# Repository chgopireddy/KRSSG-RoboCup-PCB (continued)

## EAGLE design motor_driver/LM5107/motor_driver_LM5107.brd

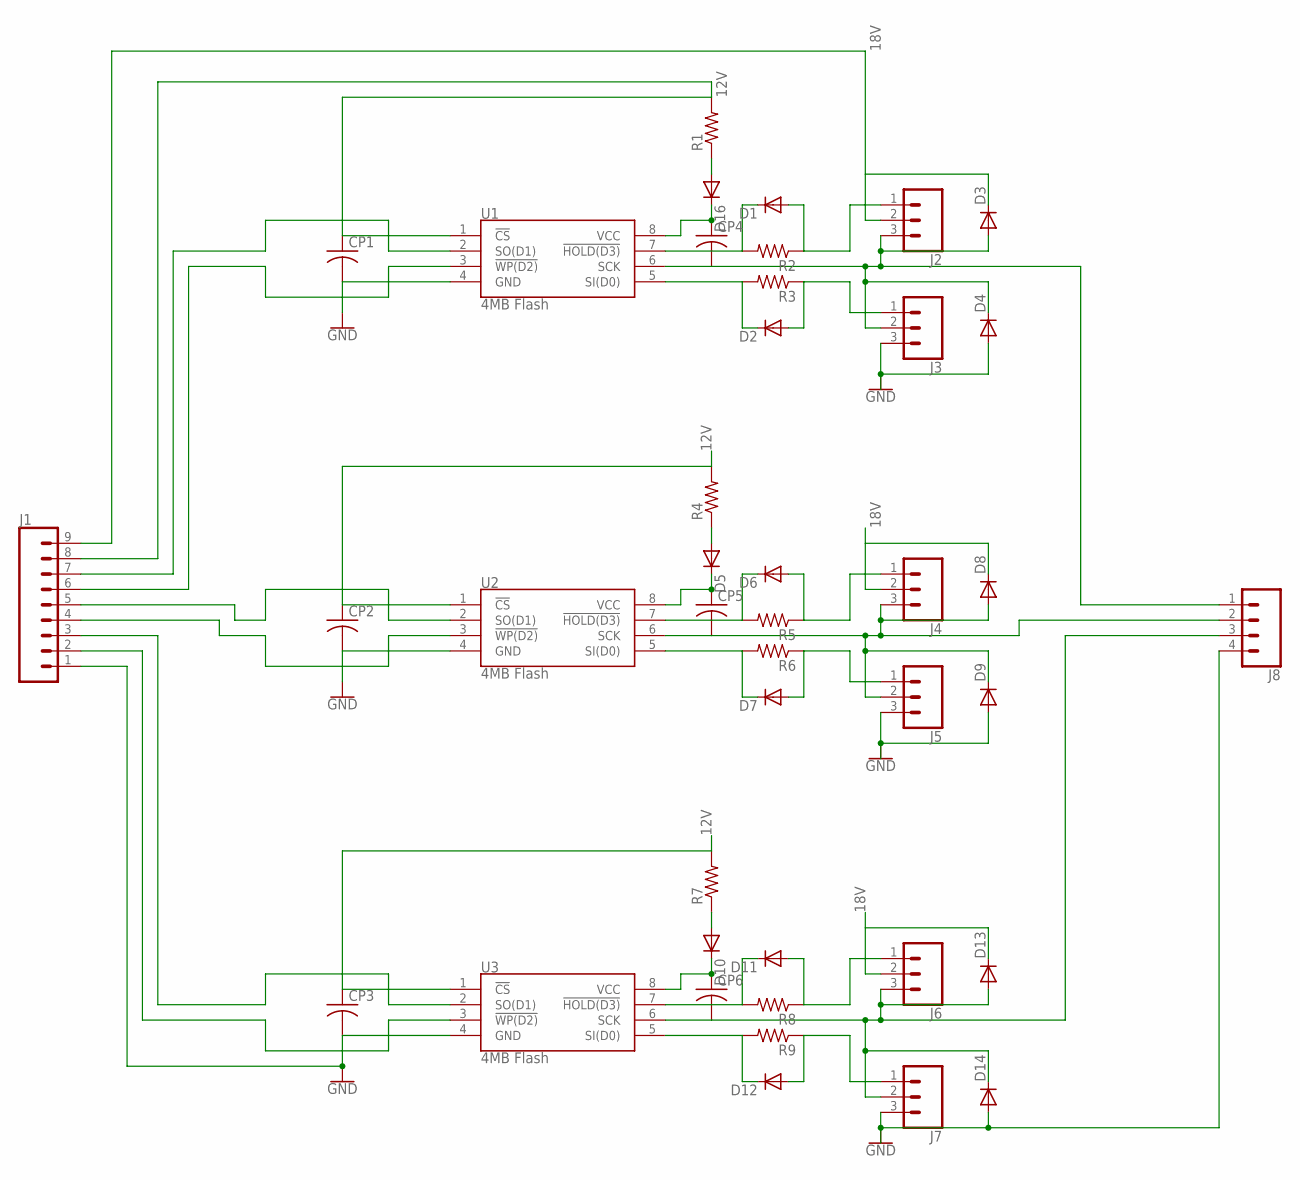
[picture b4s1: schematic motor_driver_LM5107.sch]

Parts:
CP1, CP2, CP3, CP4, CP5, CP6: C-US025-024X044; C025-024X044
D1, D2, D3, D4, D5, D6, D7, D8, D9, D10, D11, D12, D13, D14, D16: DIODE-D-5; D-5
J1: CONN_09; 1X09
J2, J3, J4, J5, J6, J7: CONN_03LOCK; 1X03_LOCK
J8: CONN_04; 1X04
R1, R2, R3, R4, R5, R6, R7, R8, R9: R-US_0204/5; 0204/5
U1, U2, U3: 4MB Flash; SO08

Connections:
12V: CP1.1, CP2.1, CP3.1, J1.8, R1.2, R4.2, R7.2, U1.1 (!CS), U2.1 (!CS), U3.1 (!CS)
18V: D3.C, D8.C, D13.C, J1.9, J2.2, J4.2, J6.2
GND: CP1.2, CP2.2, CP3.2, D4.A, D9.A, D14.A, J1.1, J3.3, J5.3, J7.3, J8.4, U1.4 (GND), U2.4 (GND), U3.4 (GND)
unnamed: D16.A, R1.1
unnamed: CP4.1, D16.C, U1.8 (VCC)
unnamed: D1.C, R2.2, U1.7 (!HOLD(D3))
unnamed: CP4.2, D3.A, D4.C, J2.3, J3.2, J8.1, U1.6 (SCK)
unnamed: J1.7, U1.2 (SO(D1))
unnamed: J1.6, U1.3 (!WP(D2))
unnamed: D2.C, R3.2, U1.5 (SI(D0))
unnamed: D1.A, J2.1, R2.1
unnamed: D2.A, J3.1, R3.1
unnamed: D5.A, R4.1
unnamed: CP5.1, D5.C, U2.8 (VCC)
unnamed: CP5.2, D8.A, D9.C, J4.3, J5.2, J8.2, U2.6 (SCK)
unnamed: J1.5, U2.2 (SO(D1))
unnamed: J1.4, U2.3 (!WP(D2))
unnamed: D6.C, R5.2, U2.7 (!HOLD(D3))
unnamed: D7.C, R6.2, U2.5 (SI(D0))
unnamed: D6.A, J4.1, R5.1
unnamed: D7.A, J5.1, R6.1
unnamed: D10.A, R7.1
unnamed: CP6.1, D10.C, U3.8 (VCC)
unnamed: CP6.2, D13.A, D14.C, J6.3, J7.2, J8.3, U3.6 (SCK)
unnamed: J1.3, U3.2 (SO(D1))
unnamed: J1.2, U3.3 (!WP(D2))
unnamed: D11.C, R8.2, U3.7 (!HOLD(D3))
unnamed: D12.C, R9.2, U3.5 (SI(D0))
unnamed: D11.A, J6.1, R8.1
unnamed: D12.A, J7.1, R9.1

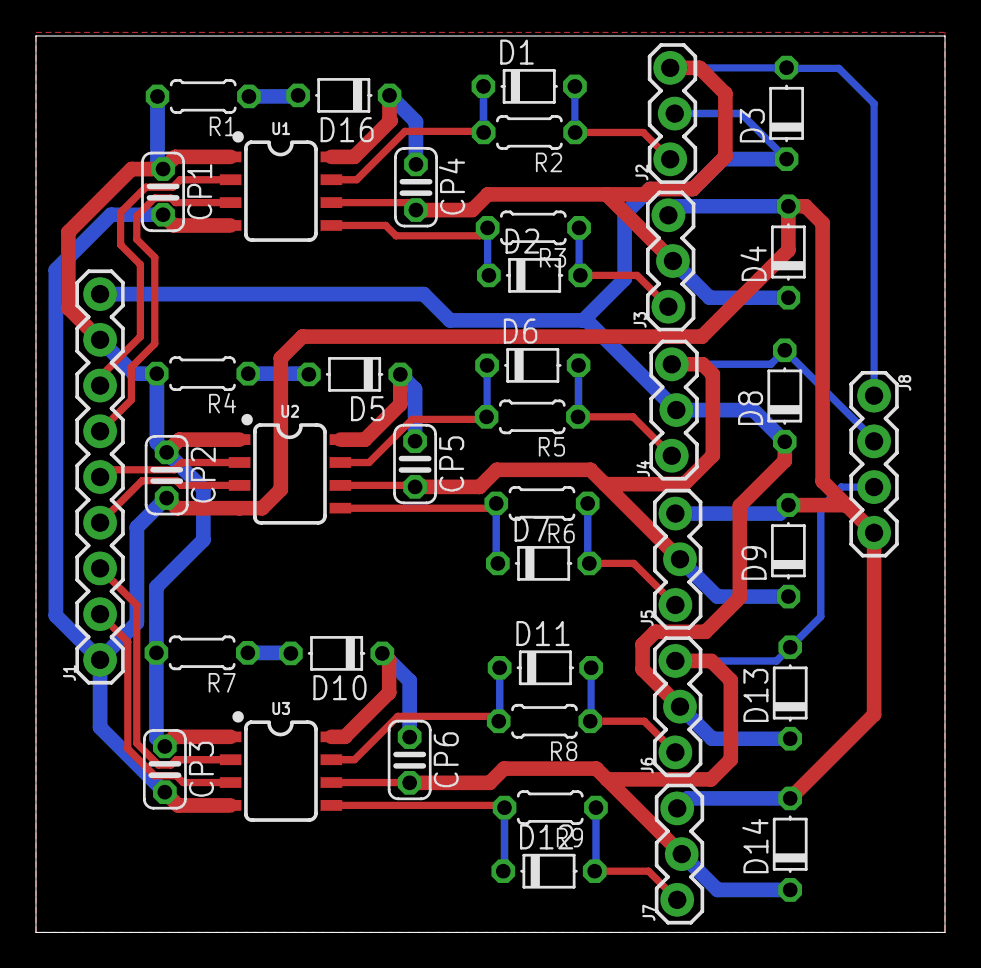
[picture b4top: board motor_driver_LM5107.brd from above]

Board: 2 copper layers, 50.5 x 49.8 mm, 41 parts (0 on the bottom side), 30 nets.

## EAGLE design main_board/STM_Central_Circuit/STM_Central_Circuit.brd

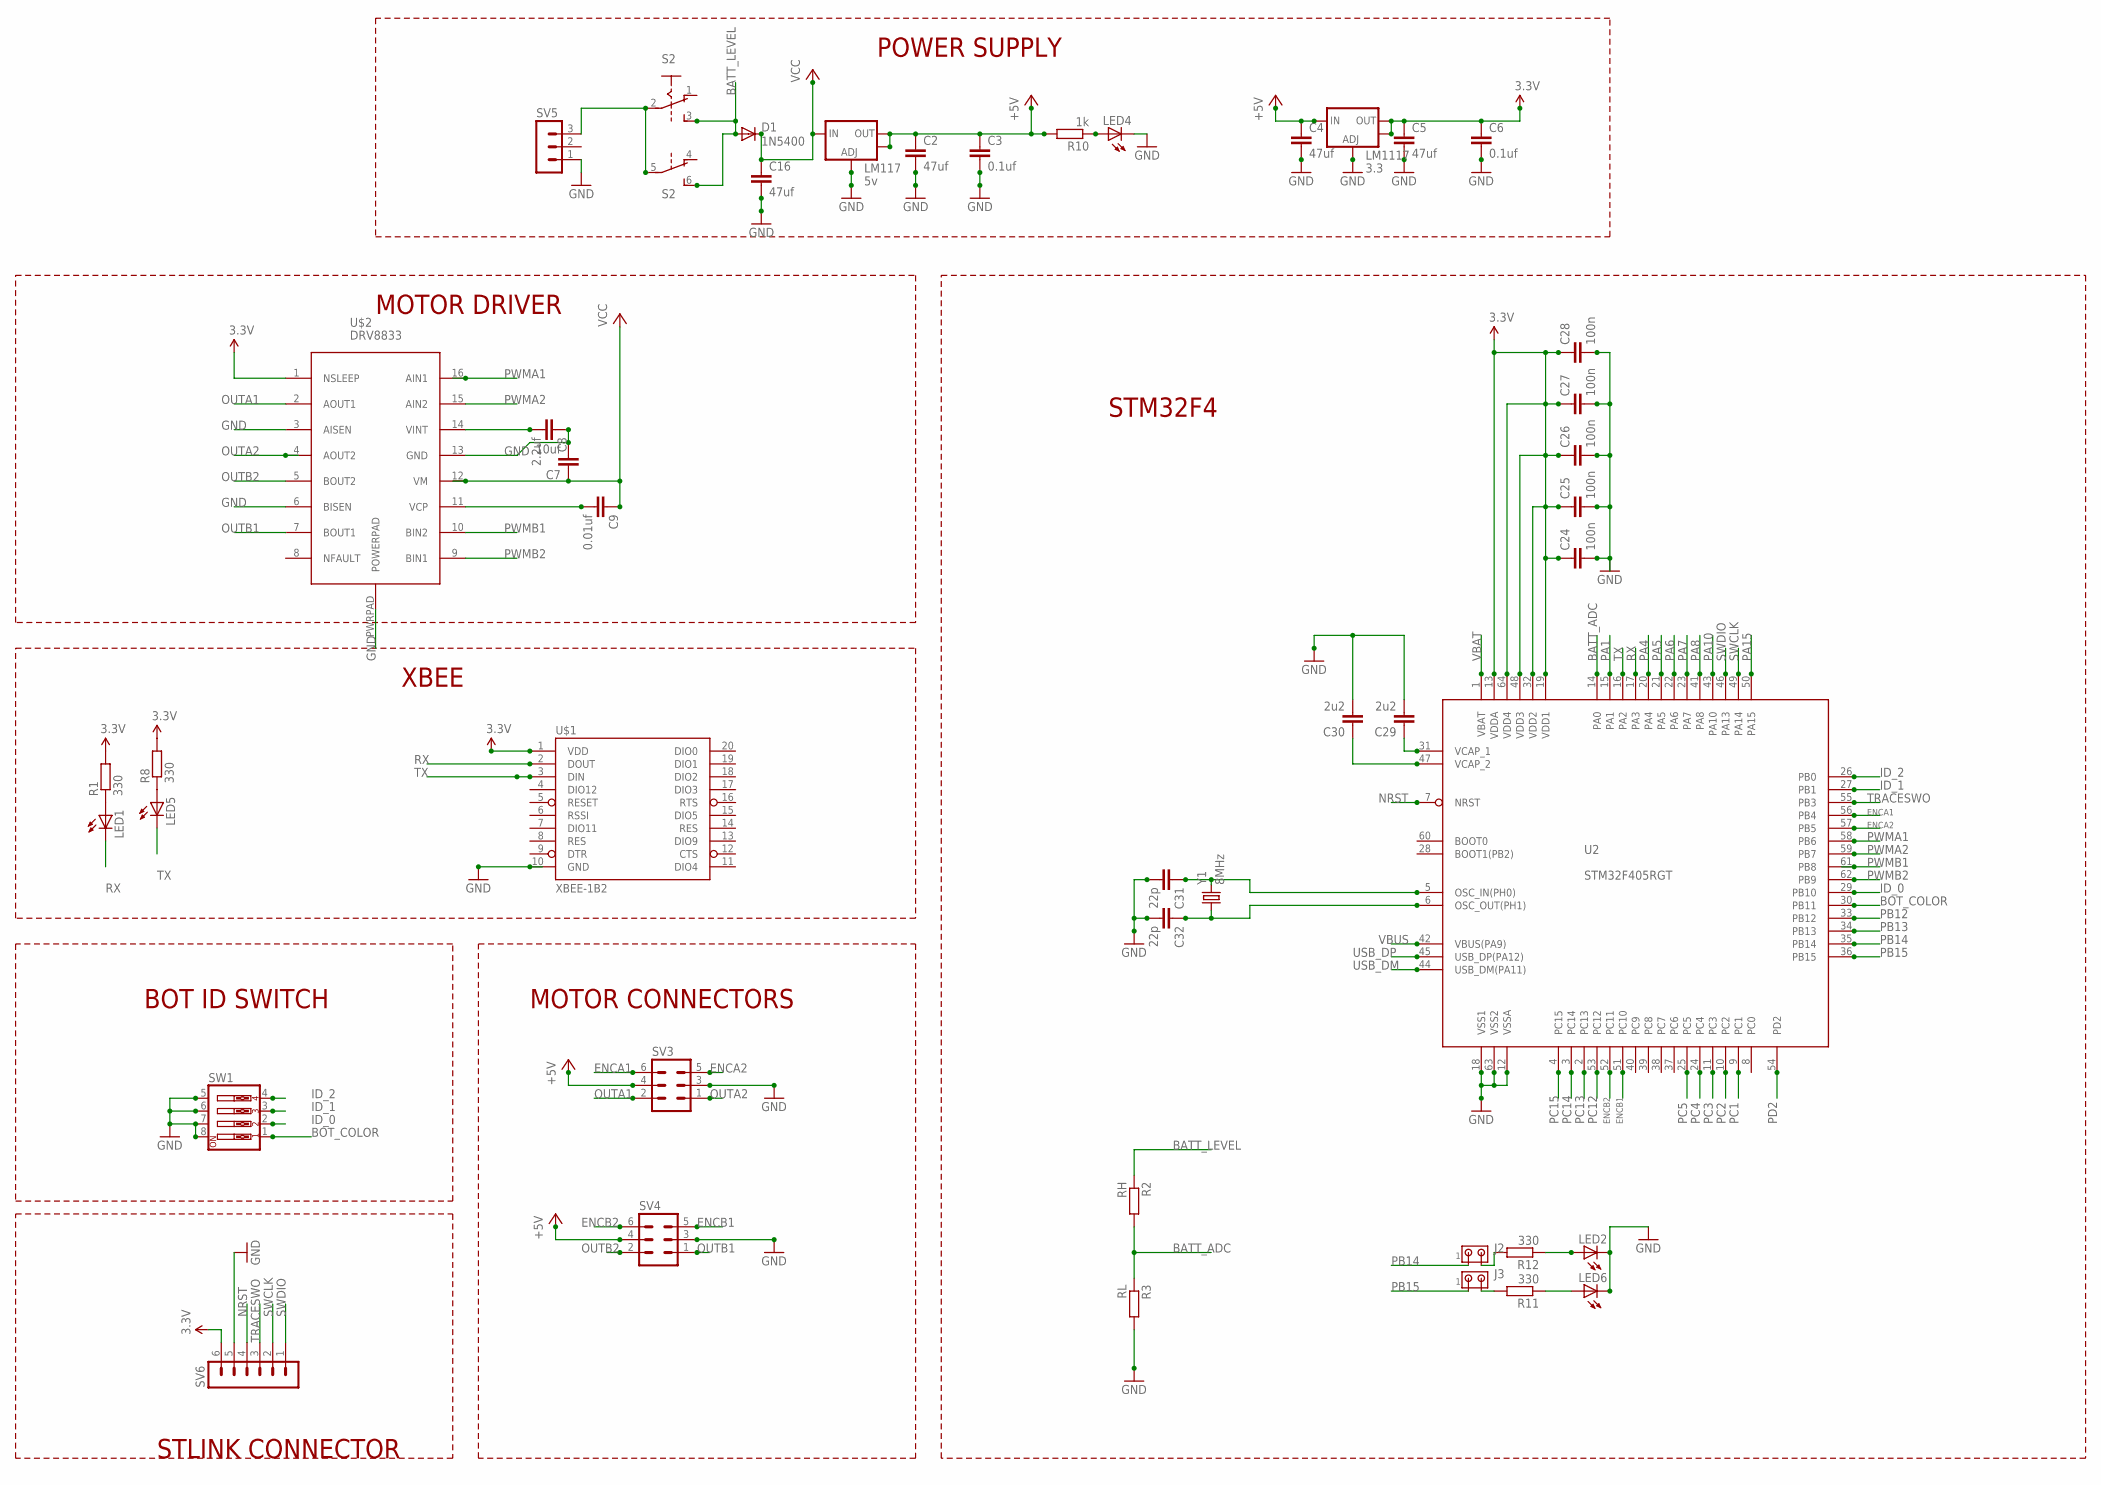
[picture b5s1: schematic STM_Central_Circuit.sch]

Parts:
C2, C4, C5, C16: 47uf; C1206
C3, C6: 0.1uf; C1206
C7: 10uf; C1206
C8: 2.2uf; C1206
C9: 0.01uf; C1206
C24, C25, C26, C27, C28: 100n; 0603-CAP
C29, C30: 2u2; 0603-CAP
C31, C32: 22p; 0603-CAP
D1: 1N5400; DO201-15
J2, J3: MTA02-100; 10X02MTA
LED1, LED2, LED4, LED5, LED6: LED5MM
LM117: 5v; SOT223
LM1117: 3.3; SOT223
R1, R8, R11, R12: 330; 0207/10
R2: RH; 0207/10
R3: RL; 0207/10
R10: 1k; 0207/10
S2: A68-A31
SV3, SV4: MA03-2
SV5: MA03-1
SV6: MA06-1
SW1: SW_DIP-4; EDG-04
U2: STM32F405RGT; LQFP64
U$1: XBEE-1B2; XBEE-SILK
U$2: DRV8833; PWP_R_PDSO_G16
Y1: 8MHz; CRYSTAL-SMD-5X3

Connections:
3.3V: C5.1, C6.1, C24.1, C25.1, C26.1, C27.1, C28.1, LM1117.2 (OUT), LM1117.4 (OUT), R1.2, R8.2, SV6.6, U2.13 (VDDA), U2.19 (VDD1), U2.32 (VDD2), U2.48 (VDD3), U2.64 (VDD4), U$1.1 (VDD), U$2.1 (NSLEEP)
+5V: C2.1, C3.1, C4.1, LM117.2 (OUT), LM117.4 (OUT), LM1117.3 (IN), R10.2, SV3.4, SV4.4
BATT_ADC: R2.2, R3.1, U2.14 (PA0)
BATT_LEVEL: D1.A, R2.1, S2.3 (S), S2.6 (S)
BOT_COLOR: SW1.1, U2.30 (PB11)
ENCA1: SV3.6, U2.56 (PB4)
ENCA2: SV3.5, U2.57 (PB5)
ENCB1: SV4.5, U2.51 (PC10)
ENCB2: SV4.6, U2.52 (PC11)
GND: C2.2, C3.2, C4.2, C5.2, C6.2, C7.2, C8.1, C16.2, C24.2, C25.2, C26.2, C27.2, C28.2, C29.2, C30.2, C31.2, C32.2, LED2.K (C), LED4.K (C), LED6.K (C), LM117.1 (ADJ), LM1117.1 (ADJ), R3.2, SV3.3, SV4.3, SV5.1, SV6.5, SW1.5, SW1.6, SW1.7, SW1.8, U2.12 (VSSA), U2.18 (VSS1), U2.63 (VSS2), U$1.10 (GND), U$2.3 (AISEN), U$2.6 (BISEN), U$2.13 (GND), U$2.PWRPAD (POWERPAD)
ID_0: SW1.2, U2.29 (PB10)
ID_1: SW1.3, U2.27 (PB1)
ID_2: SW1.4, U2.26 (PB0)
unnamed: LED1.A, R1.1
unnamed: LED6.A, R11.1
unnamed: J2.2, R12.2
unnamed: LED4.A, R10.1
unnamed: LED5.A, R8.1
unnamed: C8.2, U$2.14 (VINT)
unnamed: J3.2, R11.2
unnamed: LED2.A, R12.1
unnamed: S2.2, S2.5, SV5.3
unnamed: C9.2, U$2.11 (VCP)
unnamed: C29.1, U2.31 (VCAP_1)
unnamed: C30.1, U2.47 (VCAP_2)
unnamed: C32.1, U2.6 (OSC_OUT(PH1)), Y1.1
unnamed: C31.1, U2.5 (OSC_IN(PH0)), Y1.3 (2)
NRST: SV6.4, U2.7 (NRST)
OUTA1: SV3.2, U$2.2 (AOUT1)
OUTA2: SV3.1, U$2.4 (AOUT2)
OUTB1: SV4.1, U$2.7 (BOUT1)
OUTB2: SV4.2, U$2.5 (BOUT2)
PA1: U2.15 (PA1)
PA4: U2.20 (PA4)
PA5: U2.21 (PA5)
PA6: U2.22 (PA6)
PA7: U2.23 (PA7)
PA8: U2.41 (PA8)
PA10: U2.43 (PA10)
PA15: U2.50 (PA15)
PB12: U2.33 (PB12)
PB13: U2.34 (PB13)
PB14: J2.1, U2.35 (PB14)
PB15: J3.1, U2.36 (PB15)
PC1: U2.9 (PC1)
PC2: U2.10 (PC2)
PC3: U2.11 (PC3)
PC4: U2.24 (PC4)
PC5: U2.25 (PC5)
PC12: U2.53 (PC12)
PC13: U2.2 (PC13)
PC14: U2.3 (PC14)
PC15: U2.4 (PC15)
PD2: U2.54 (PD2)
PWMA1: U2.58 (PB6), U$2.16 (AIN1)
PWMA2: U2.59 (PB7), U$2.15 (AIN2)
PWMB1: U2.61 (PB8), U$2.10 (BIN2)
PWMB2: U2.62 (PB9), U$2.9 (BIN1)
RX: LED1.K (C), U2.17 (PA3), U$1.2 (DOUT)
SWCLK: SV6.2, U2.49 (PA14)
SWDIO: SV6.1, U2.46 (PA13)
TRACESWO: SV6.3, U2.55 (PB3)
TX: LED5.K (C), U2.16 (PA2), U$1.3 (DIN)
USB_DM: U2.44 (USB_DM(PA11))
USB_DP: U2.45 (USB_DP(PA12))
VBAT: U2.1 (VBAT)
VBUS: U2.42 (VBUS(PA9))
VCC: C7.1, C9.1, C16.1, D1.C, LM117.3 (IN), U$2.12 (VM)

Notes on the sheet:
BOT ID SWITCH
MOTOR CONNECTORS
XBEE
MOTOR DRIVER
STM32F4
POWER SUPPLY
STLINK CONNECTOR

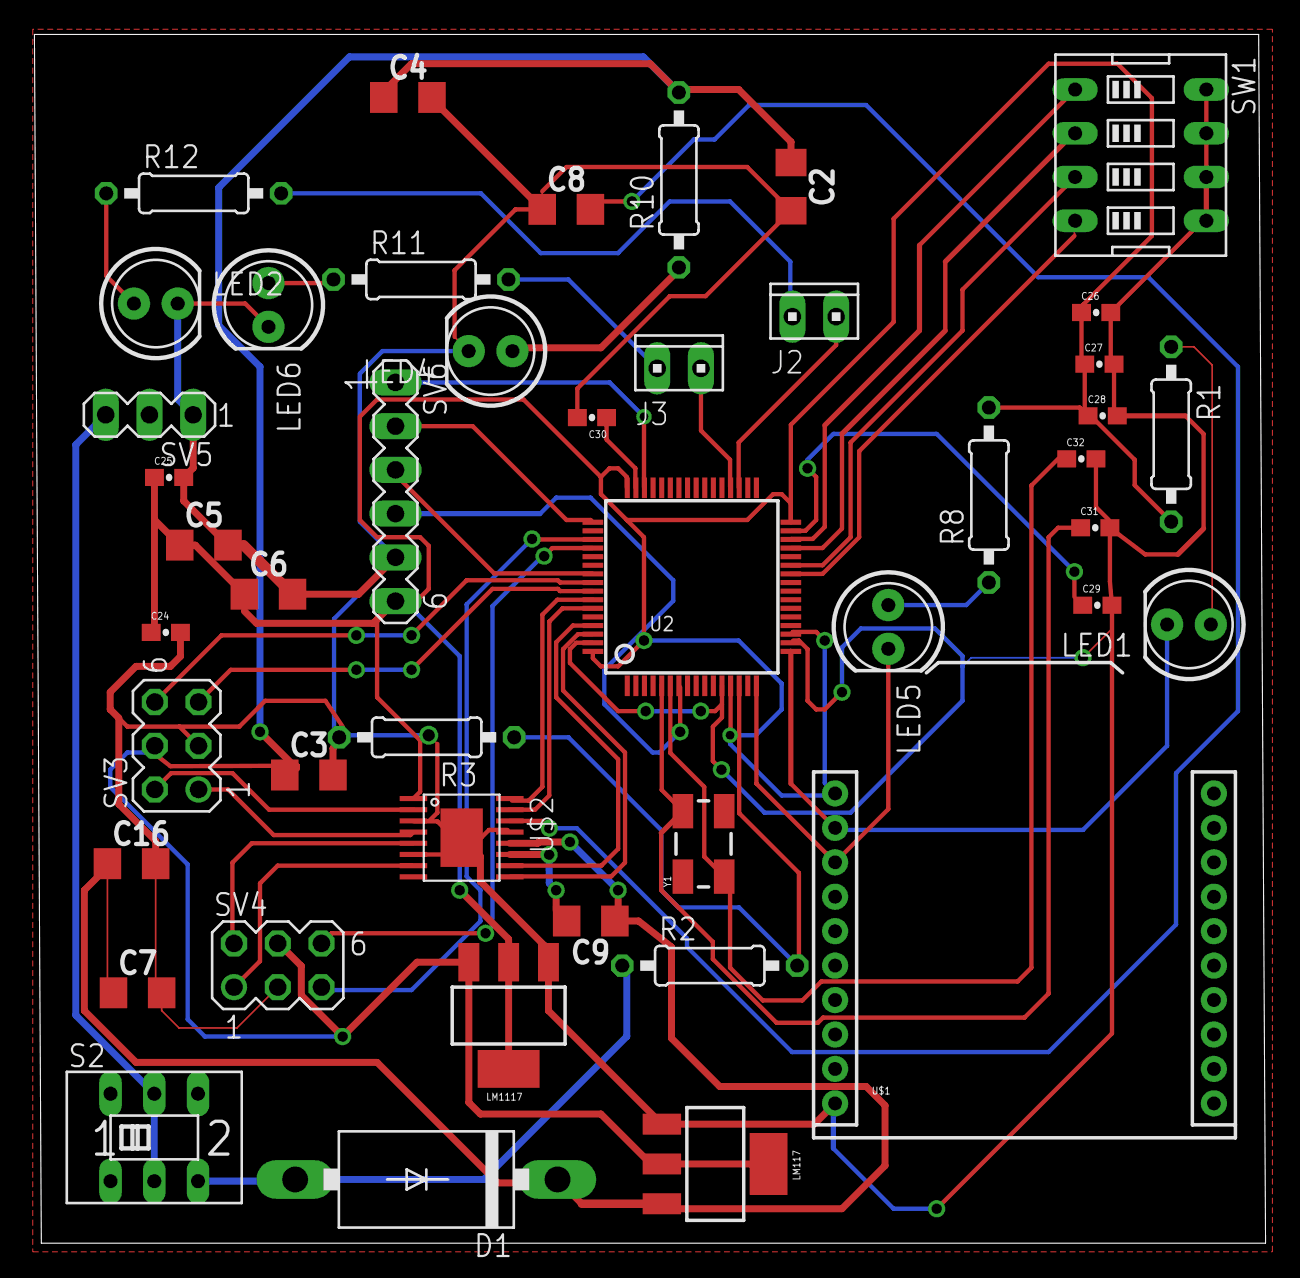
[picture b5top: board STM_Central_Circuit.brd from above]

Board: 2 copper layers, 71.5 x 70.2 mm, 45 parts (0 on the bottom side), 44 nets.

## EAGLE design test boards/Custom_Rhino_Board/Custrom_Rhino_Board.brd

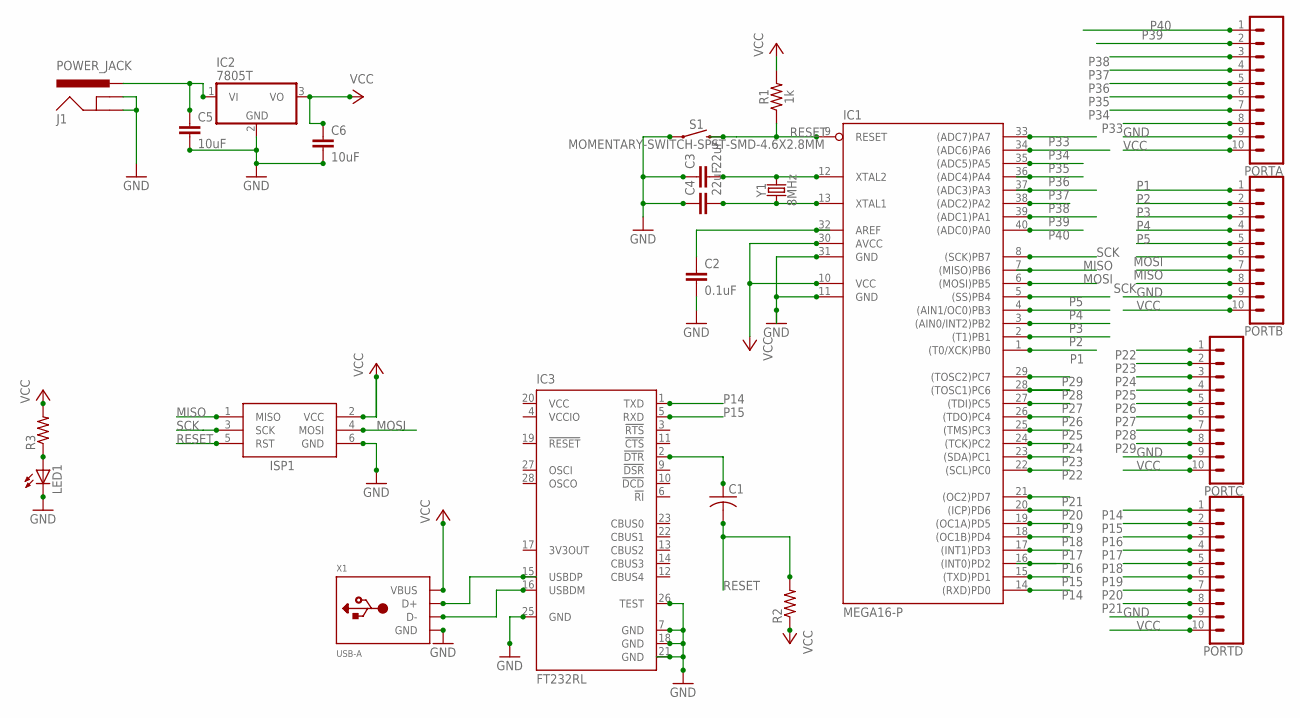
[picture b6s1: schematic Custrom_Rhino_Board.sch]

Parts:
C1: C-US025-024X044; C025-024X044
C2: 0.1uF; 0603
C3, C4: 22uF; 0805
C5, C6: 10uF; 0805
IC1: MEGA16-P; DIL40
IC2: 7805T; TO220H
IC3: FT232RL; SSOP28
ISP1: AVRISP-6; AVRISP
J1: POWER_JACK; POWER_JACK_PTH
LED1: LEDCHIP-LED0603; CHIP-LED0603
PORTA: CONN_10"; 1X10
PORTB: CONN_10"; 1X10
PORTC: CONN_10"; 1X10
PORTD: CONN_10"; 1X10
R1: 1k; AXIAL-0.3
R2, R3: R-US_0204/5; 0204/5
S1: MOMENTARY-SWITCH-SPST-SMD-4.6X2.8MM; TACTILE_SWITCH_SMD_4.6X2.8MM
X1: USB-A; MOLEX_480371000
Y1: 8MHz; HC49UP

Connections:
GND: C2.2, C3.1, C4.1, C5.2, C6.2, IC1.11 (GND), IC1.31 (GND), IC2.2 (GND), IC3.7 (GND), IC3.18 (GND), IC3.21 (GND), IC3.25 (GND), IC3.26 (TEST), ISP1.6 (GND), J1.GND, J1.GNDBREAK, LED1.C, PORTA.9, PORTB.9, PORTC.9, PORTD.9, S1.1, S1.2 (1), X1.4 (GND)
MISO: IC1.7 ((MISO)PB6), ISP1.1 (MISO), PORTB.7
MOSI: IC1.6 ((MOSI)PB5), ISP1.4 (MOSI), PORTB.6
unnamed: C2.1, IC1.32 (AREF)
unnamed: C1.1, IC3.2 (!DTR)
unnamed: C3.2, IC1.12 (XTAL2), Y1.2
unnamed: C4.2, IC1.13 (XTAL1), Y1.1
unnamed: C5.1, IC2.1 (VI), J1.PWR
unnamed: IC3.15 (USBDP), X1.3 (D+)
unnamed: IC3.16 (USBDM), X1.2 (D-)
unnamed: LED1.A, R3.1
P1: IC1.1 ((T0/XCK)PB0), PORTB.1
P2: IC1.2 ((T1)PB1), PORTB.2
P3: IC1.3 ((AIN0/INT2)PB2), PORTB.3
P4: IC1.4 ((AIN1/OC0)PB3), PORTB.4
P5: IC1.5 ((SS)PB4), PORTB.5
P14: IC1.14 ((RXD)PD0), IC3.1 (TXD), PORTD.1
P15: IC1.15 ((TXD)PD1), IC3.5 (RXD), PORTD.2
P16: IC1.16 ((INT0)PD2), PORTD.3
P17: IC1.17 ((INT1)PD3), PORTD.4
P18: IC1.18 ((OC1B)PD4), PORTD.5
P19: IC1.19 ((OC1A)PD5), PORTD.6
P20: IC1.20 ((ICP)PD6), PORTD.7
P21: IC1.21 ((OC2)PD7), PORTD.8
P22: IC1.22 ((SCL)PC0), PORTC.1
P23: IC1.23 ((SDA)PC1), PORTC.2
P24: IC1.24 ((TCK)PC2), PORTC.3
P25: IC1.25 ((TMS)PC3), PORTC.4
P26: IC1.26 ((TDO)PC4), PORTC.5
P27: IC1.27 ((TDI)PC5), PORTC.6
P28: IC1.28 ((TOSC1)PC6), PORTC.7
P29: IC1.29 ((TOSC2)PC7), PORTC.8
P33: IC1.33 ((ADC7)PA7), PORTA.8
P34: IC1.34 ((ADC6)PA6), PORTA.7
P35: IC1.35 ((ADC5)PA5), PORTA.6
P36: IC1.36 ((ADC4)PA4), PORTA.5
P37: IC1.37 ((ADC3)PA3), PORTA.4
P38: IC1.38 ((ADC2)PA2), PORTA.3
P39: IC1.39 ((ADC1)PA1), PORTA.2
P40: IC1.40 ((ADC0)PA0), PORTA.1
RESET: C1.2, IC1.9 (RESET), ISP1.5 (RST), R1.P$1 (1), R2.2, S1.3 (2), S1.4 (2)
SCK: IC1.8 ((SCK)PB7), ISP1.3 (SCK), PORTB.8
VCC: C6.1, IC1.10 (VCC), IC1.30 (AVCC), IC2.3 (VO), IC3.20 (VCC), ISP1.2 (VCC), PORTA.10, PORTB.10, PORTC.10, PORTD.10, R1.P$2 (2), R2.1, R3.2, X1.1 (VBUS)
VCCIO: IC3.4 (VCCIO)

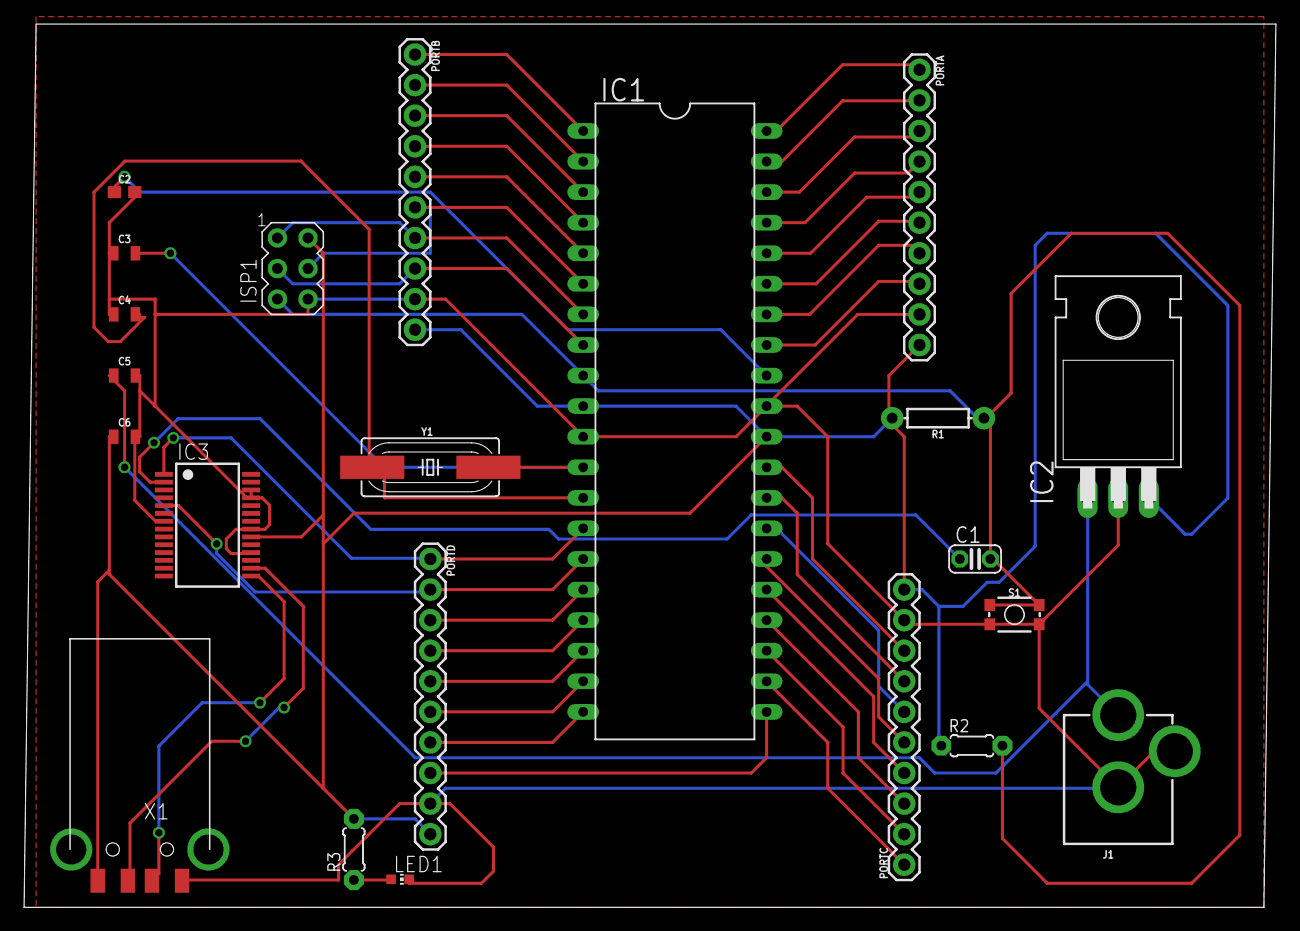
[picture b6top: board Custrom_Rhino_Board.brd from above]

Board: 2 copper layers, 104.0 x 73.4 mm, 22 parts (0 on the bottom side), 43 nets.

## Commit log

2019-09-15 Final Kicker Circuit schematic
2019-09-15 Final Kicker Circuit Board
2019-09-15 Solenoid Kicker Circuits
2019-09-15 Solenoid Kicker Circuit
2019-09-15 Central control Circuit
2019-09-15 BLDC Motor Driver
2019-09-15 BLDC Motor Controller
2019-09-15 Library for Esp32, IR4427
